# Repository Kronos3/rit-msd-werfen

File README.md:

# RIT-Werfen Inspection

## Overview

Layout for this project:
  - /pcb - KiCAD Design file for the PCB
  - /mc - Microcontroller firmware for STM32L476RG
  - /prototyping - Test images and Jupyter Notebooks used to prototype code
  - /src - Code running on the Raspberry Pi and in the browser
    - frontend/ - ReactJS (Typescript) program for frontend browser code
    - rit/ - Middleware that abstract the behavior of cameras and MC packet interface
    - web/ - FastAPI that exposes webendpoints for the frontend to submit requests to
    - camera_focusing.py - Script that boots up a QT Program to view the camera live

## Building

The microcontroller code can be built using CMake + GCC Arm toolchain.
You should use a relatively recent GCC Arm toolchain (`arm-none-eabi-gcc`)

### Dependency installation (Ubuntu)

On Ubuntu, run the following to install the dependencies:

```
sudo apt install gcc-arm-none-eabi cmake make
```

### Building PCB code

```
mkdir -p mc/build
cd mc/build
cmake -DCMAKE_C_COMPILER=arm-none-eabi-gcc -DCMAKE_CXX_COMPILER=arm-none-eabi-g++ ../
```

Now that the code is built, you can flash the PCB using an ST-Link or the ST-Link found on a STM32 Nucleo board using SWD via OpenOCD. I'd recommend using a Nucleo board for flashing along with an IDE like CLion that can set up, build and flash firmware for you.

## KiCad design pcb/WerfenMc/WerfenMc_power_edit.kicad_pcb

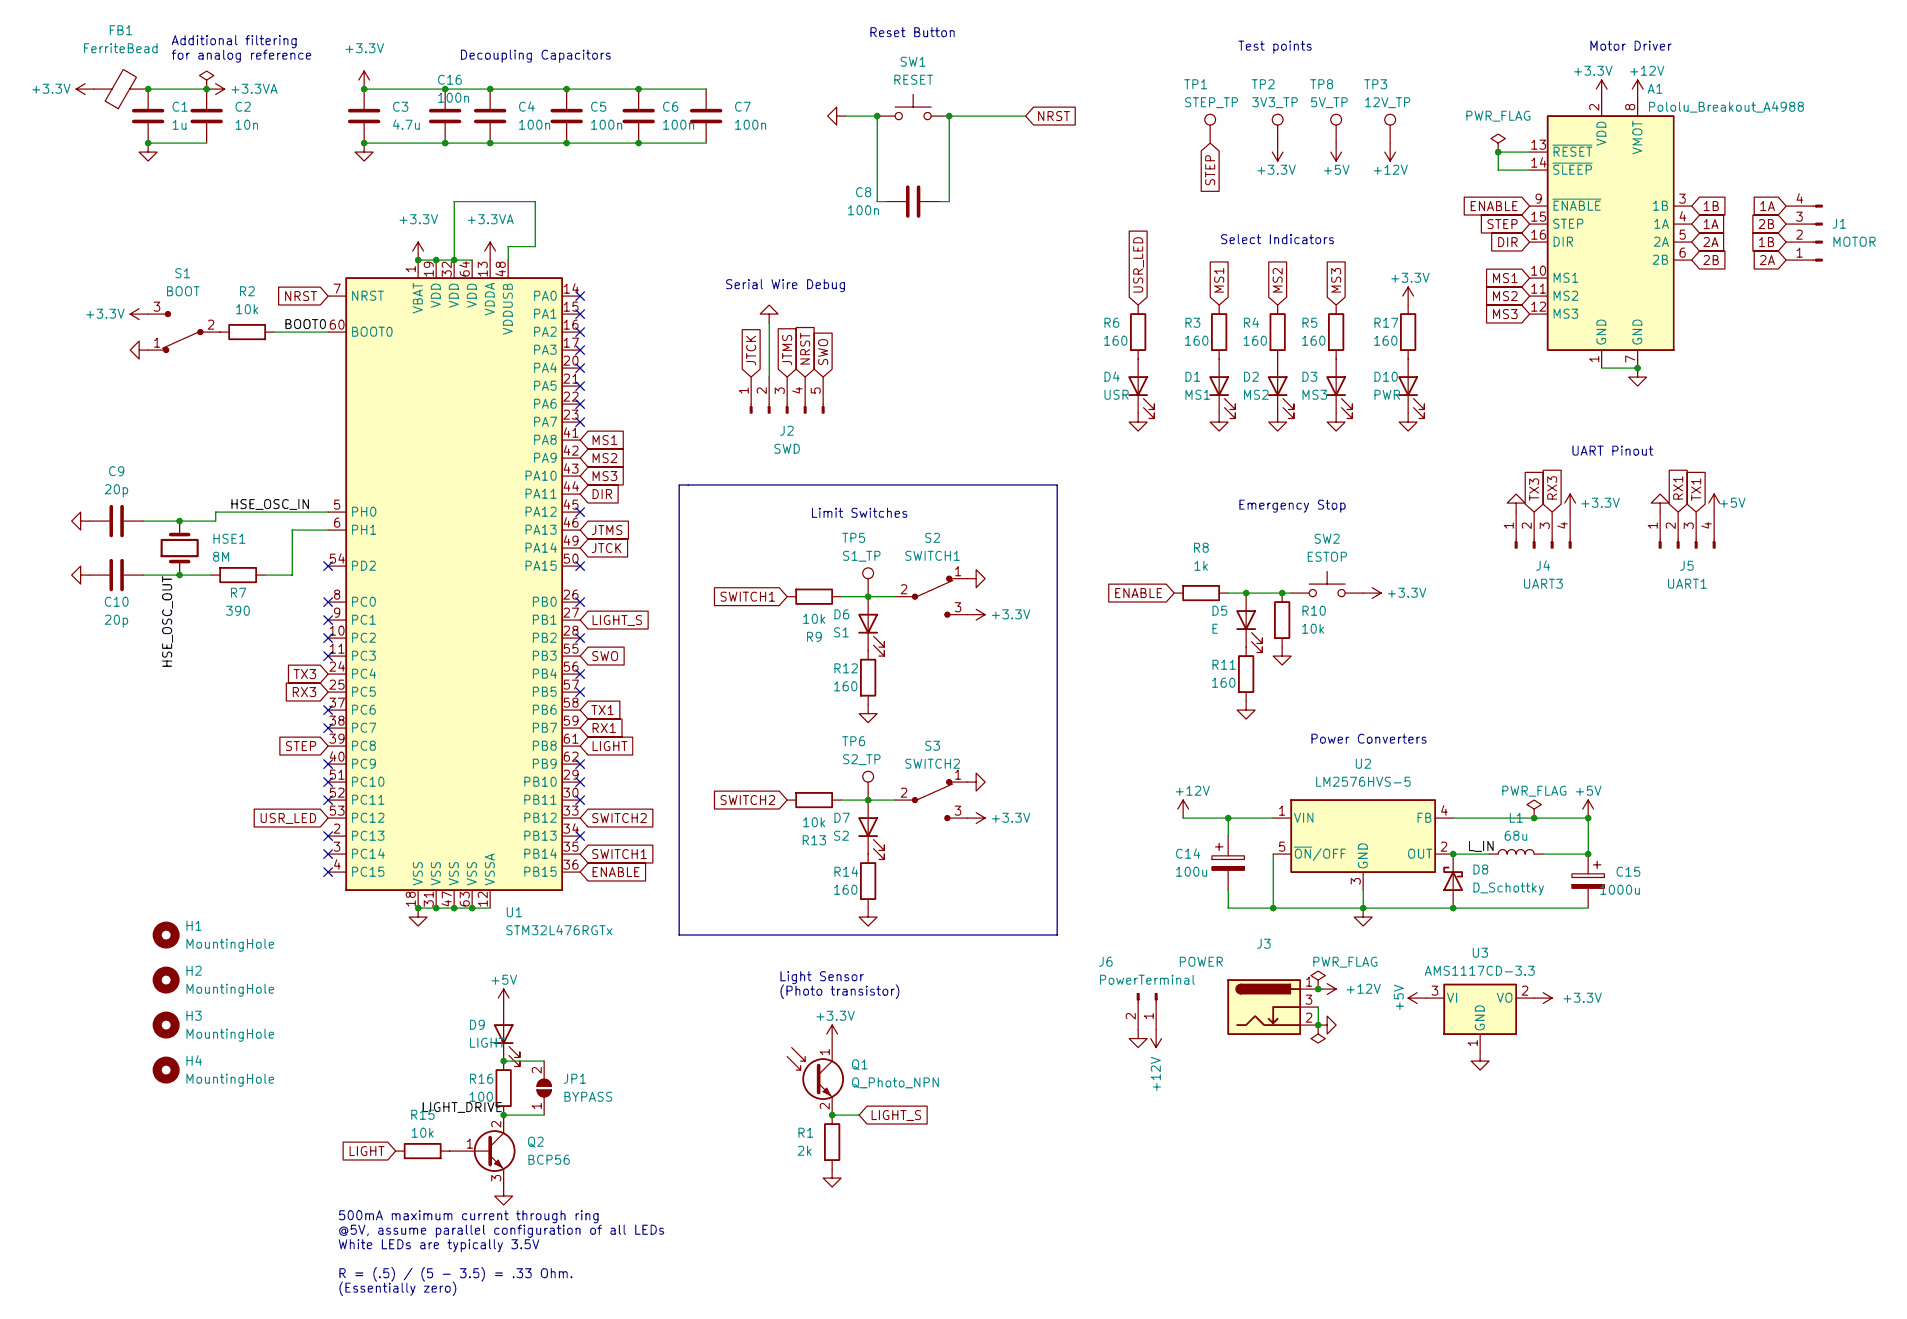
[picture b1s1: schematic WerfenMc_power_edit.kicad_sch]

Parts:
A1: Pololu_Breakout_A4988; Pololu_Breakout-16_15.2x20.3mm
C1: 1u; CP_EIA-2012-12_Kemet-R
C2: 10n; CP_EIA-2012-12_Kemet-R
C3: 4.7u; CP_EIA-2012-12_Kemet-R
C4, C5, C6, C7, C8, C16: 100n; C_0402_1005Metric
C9, C10: 20p; C_0402_1005Metric
C14: 100u; C_Elec_8x5.4
C15: 1000u; C_Elec_8x5.4
D1: MS1; LED_0805_2012Metric
D2: MS2; LED_0805_2012Metric
D3: MS3; LED_0805_2012Metric
D4: USR; LED_0805_2012Metric
D5: E; LED_0805_2012Metric
D6: S1; LED_0805_2012Metric
D7: S2; LED_0805_2012Metric
D8: D_Schottky; D_SMC
D9: LIGHT; TerminalBlock_Phoenix_MPT-0,5-2-2.54_1x02_P2.54mm_Horizontal
D10: PWR; LED_0805_2012Metric
FB1: FerriteBead; L_0603_1608Metric
H1, H2, H3, H4: MountingHole; MountingHole_2.2mm_M2
HSE1: 8M; Crystal_SMD_MicroCrystal_CC4V-T1A-2Pin_5.0x1.9mm
J1: MOTOR; PinHeader_1x04_P2.54mm_Vertical
J2: SWD; PinHeader_1x05_P2.54mm_Vertical
J3: POWER; BarrelJack_Horizontal
J4: UART3; PinHeader_1x04_P2.54mm_Vertical
J5: UART1; PinHeader_1x04_P2.54mm_Vertical
J6: PowerTerminal; TerminalBlock_Phoenix_MPT-0,5-2-2.54_1x02_P2.54mm_Horizontal
JP1: BYPASS; SolderJumper-2_P1.3mm_Open_Pad1.0x1.5mm
L1: 68u; SRP1040VA-1R5M
Q1: Q_Photo_NPN; PinHeader_1x02_P2.54mm_Vertical
Q2: BCP56; SOT-223
R1: 2k; R_Axial_DIN0411_L9.9mm_D3.6mm_P15.24mm_Horizontal
R2, R9, R10, R13, R15: 10k; R_0402_1005Metric
R3, R4, R5, R6, R11, R12, R14, R17: 160; R_0402_1005Metric
R7: 390; R_0402_1005Metric
R8: 1k; R_0402_1005Metric
R16: 100; R_0603_1608Metric
S1: BOOT; Switch_Slide_11.6x4mm_EG1218; MPN EG1218; Digi-Key_PN EG1903-ND
S2: SWITCH1; PinHeader_1x03_P2.54mm_Vertical; MPN EG1218; Digi-Key_PN EG1903-ND
S3: SWITCH2; PinHeader_1x03_P2.54mm_Vertical; MPN EG1218; Digi-Key_PN EG1903-ND
SW1: RESET; SW_PUSH_6mm
SW2: ESTOP; PinHeader_1x02_P2.54mm_Vertical
TP1: STEP_TP; TestPoint_Pad_D1.5mm
TP2: 3V3_TP; TestPoint_Pad_D1.5mm
TP3: 12V_TP; TestPoint_Pad_D1.5mm
TP5: S1_TP; TestPoint_Pad_D1.5mm
TP6: S2_TP; TestPoint_Pad_D1.5mm
TP8: 5V_TP; TestPoint_Pad_D1.5mm
U1: STM32L476RGTx; LQFP-64_10x10mm_P0.5mm
U2: LM2576HVS-5; TO-263-5_TabPin3
U3: AMS1117CD-3.3; TO-252-3_TabPin2

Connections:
1A: A1.4 (1A), J1.4
1B: A1.3 (1B), J1.2
2A: A1.5 (2A), J1.1
2B: A1.6 (2B), J1.3
+3.3V: A1.2 (VDD), C3.1, C4.1, C5.1, C6.1, C7.1, C16.1, FB1.1, J4.4, Q1.1 (C), R17.1, S1.3, S2.3, S3.3, SW2.2, TP2.1, U1.1 (VBAT), U1.19 (VDD), U1.32 (VDD), U1.48 (VDDUSB), U1.64 (VDD), U3.2 (VO)
+3.3VA: C1.1, C2.1, FB1.2, U1.13 (VDDA)
+5V: C15.1, D9.1 (A), J5.4, L1.2, TP8.1, U2.4 (FB), U3.3 (VI)
+12V: A1.8 (VMOT), C14.1, J3.1, J6.1, TP3.1, U2.1 (VIN)
/BOOT0: R2.2, U1.60 (BOOT0)
/HSE_OSC_IN: C9.2, HSE1.2, U1.5 (PH0)
/HSE_OSC_OUT: C10.2, HSE1.1, R7.2
/LIGHT_DRIVE: JP1.1 (A), Q2.2 (C), Q2.4 (C), R16.2
/L_IN: D8.1 (K), L1.1, U2.2 (OUT)
DIR: A1.16 (DIR), U1.44 (PA11)
ENABLE: A1.9 (~ENABLE), R8.2, U1.36 (PB15)
GND: A1.1 (GND), A1.7 (GND), C1.2, C2.2, C3.2, C4.2, C5.2, C6.2, C7.2, C8.2, C9.1, C10.1, C14.2, C15.2, C16.2, D1.1 (K), D2.1 (K), D3.1 (K), D4.1 (K), D8.2 (A), D10.1 (K), J2.2, J3.2, J3.3, J4.1, J5.1, J6.2, Q2.3 (E), R1.2, R10.2, R11.2, R12.2, R14.2, S1.1, S2.1, S3.1, SW1.1, U1.12 (VSSA), U1.18 (VSS), U1.31 (VSS), U1.47 (VSS), U1.63 (VSS), U2.3 (GND), U2.5 (~ON/OFF), U3.1 (GND)
JTCK: J2.1, U1.49 (PA14)
JTMS: J2.3, U1.46 (PA13)
LIGHT: R15.1, U1.61 (PB8)
LIGHT_S: Q1.2 (E), R1.1, U1.27 (PB1)
MS1: A1.10 (MS1), R3.1, U1.41 (PA8)
MS2: A1.11 (MS2), R4.1, U1.42 (PA9)
MS3: A1.12 (MS3), R5.1, U1.43 (PA10)
NRST: C8.1, J2.4, SW1.2, U1.7 (NRST)
unnamed: A1.13 (~RESET), A1.14 (~SLEEP)
unnamed: D1.2 (A), R3.2
unnamed: D2.2 (A), R4.2
unnamed: D3.2 (A), R5.2
unnamed: D4.2 (A), R6.2
unnamed: D5.1 (K), R11.1
unnamed: D5.2 (A), R8.1, R10.1, SW2.1
unnamed: D6.1 (K), R12.1
unnamed: D6.2 (A), R9.1, S2.2, TP5.1
unnamed: D7.1 (K), R14.1
unnamed: D7.2 (A), R13.1, S3.2, TP6.1
unnamed: D9.2 (K), JP1.2 (B), R16.1
unnamed: D10.2 (A), R17.2
unnamed: Q2.1 (B), R15.2
unnamed: R2.1, S1.2
unnamed: R7.1, U1.6 (PH1)
RX1: J5.2, U1.59 (PB7)
RX3: J4.3, U1.25 (PC5)
STEP: A1.15 (STEP), TP1.1, U1.39 (PC8)
SWITCH1: R9.2, U1.35 (PB14)
SWITCH2: R13.2, U1.33 (PB12)
SWO: J2.5, U1.55 (PB3)
TX1: J5.3, U1.58 (PB6)
TX3: J4.2, U1.24 (PC4)
USR_LED: R6.1, U1.53 (PC12)

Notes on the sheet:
UART Pinout
Serial Wire Debug
Additional filtering for analog reference
Test points
Decoupling Capacitors
Power Converters
500mA maximum current through ring @5V, assume parallel configuration of all LEDs White LEDs are typically 3.5V R = (.5) / (5 - 3.5) = .33 Ohm. (Essentially zero)
Select Indicators
Reset Button
Emergency Stop
Light Sensor (Photo transistor)
Motor Driver
Limit Switches

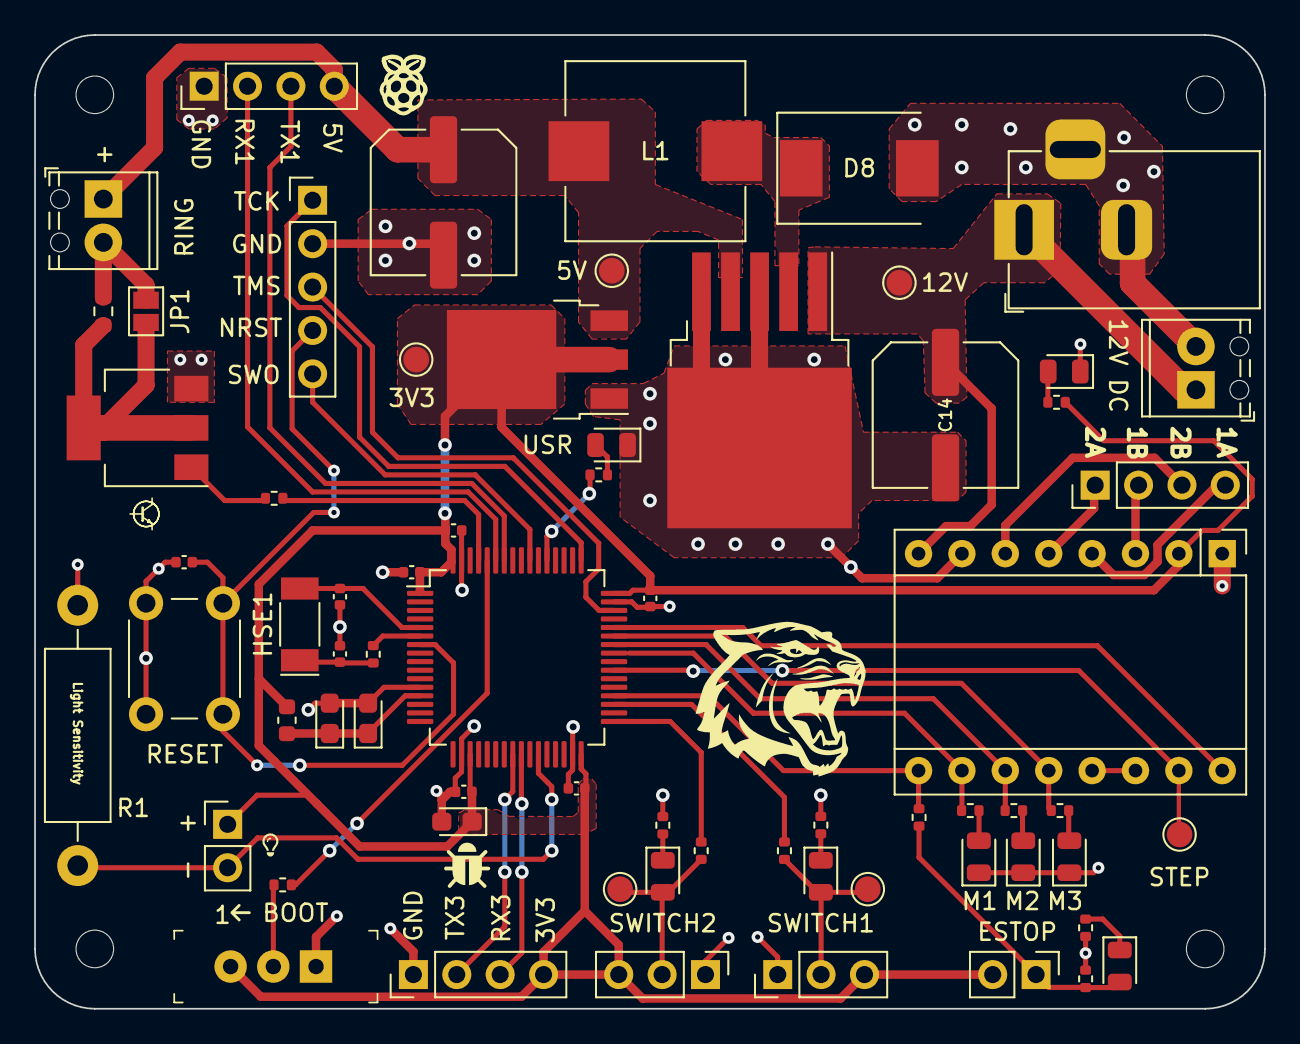
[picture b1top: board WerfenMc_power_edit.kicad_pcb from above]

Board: 2 copper layers, 72.0 x 57.0 mm, 71 parts (0 on the bottom side), 49 nets.

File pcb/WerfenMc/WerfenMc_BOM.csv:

Designator,Qnty,Comment,Name,Footprint,Description,JLCPCB Part #
"C1, ",1,1uF,C,Capacitor_Tantalum_SMD:CP_EIA-2012-12_Kemet-R,Unpolarized capacitor,C28323
"C2, ",1,10nF,C,Capacitor_Tantalum_SMD:CP_EIA-2012-12_Kemet-R,Unpolarized capacitor,C1710
"C3, ",1,4.7uF,C,Capacitor_Tantalum_SMD:CP_EIA-2012-12_Kemet-R,Unpolarized capacitor,C17779
"C4, C5, C6, C7, C8, C16, ",6,100nF,C,Capacitor_SMD:C_0402_1005Metric,Unpolarized capacitor,C1525
"C9, C10, ",2,20pF,C,Capacitor_SMD:C_0402_1005Metric,Unpolarized capacitor,C1554
"C14, ",1,100uF,C_Polarized,Capacitor_SMD:C_Elec_8x5.4,Polarized capacitor,C72481
"C15, ",1,1000uF,C_Polarized,Capacitor_SMD:C_Elec_8x5.4,Polarized capacitor,C99833
"D1, D2, D3, D4, D5, D6, D7, D10",8,LED Red,LED,LED_SMD:LED_0805_2012Metric,Light emitting diode,C84256
"D8,",1,D_Schottky,D_Schottky,Diode_SMD:D_0805_2012Metric,Schottky diode,C35722
"FB1, ",1,FerriteBead,FerriteBead,Inductor_SMD:L_0603_1608Metric,Ferrite bead,C1002
"HSE1, ",1,8MHz,Crystal,Crystal:Crystal_SMD_TXC_7A-2Pin_5x3.2mm,Two pin crystal,C115962
"Q2, ",1,BCP56,BCP56,Package_TO_SOT_SMD:SOT-223,"1A Ic, 80V Vce, NPN Medium Power Transistor, SOT-223",C95810
"R2, R9, R10, R13, R15, ",5,10k,R,Resistor_SMD:R_0402_1005Metric,Resistor,C25744
"R3, R4, R5, R6, R11, R12, R14, R17, ",8,160,R,Resistor_SMD:R_0402_1005Metric,Resistor,C25087
"R7, ",1,390,R,Resistor_SMD:R_0402_1005Metric,Resistor,C25102
"R8, ",1,1k,R,Resistor_SMD:R_0402_1005Metric,Resistor,C11702
"R16, ",1,100,R,Resistor_SMD:R_0603_1608Metric,Resistor,C22775
"U1, ",1,STM32L476RGTx,STM32L476RGTx,Package_QFP:LQFP-64_10x10mm_P0.5mm,"ARM Cortex-M4 MCU, 1024KB flash, 128KB RAM, 80MHz, 1.71-3.6V, 51 GPIO, LQFP-64",C74797
"U2, ",1,LM2576HVS-5,LM2576HVS-5,Package_TO_SOT_SMD:TO-263-5_TabPin3,"5V 3A, SIMPLE SWITCHER® Step-Down Voltage Regulator, High Voltage Input, TO-263",C234209
"U3, ",1,AMS1117CD-3.3,AMS1117CD-3.3,Package_TO_SOT_SMD:TO-252-3_TabPin2,"1A Low Dropout regulator, positive, 3.3V fixed output, TO-252",C841796

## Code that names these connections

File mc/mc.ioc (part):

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Mcu.Name=STM32L476R(C-E-G)Tx
Mcu.Package=LQFP64
Mcu.UserName=STM32L476RGTx
PA10.GPIOParameters=GPIO_Label
PA10.GPIO_Label=MS3
PA10.Signal=GPIO_Output
PA11.GPIOParameters=GPIO_Label
PA11.GPIO_Label=DIR
PA11.Signal=GPIO_Output
PA13\ (JTMS-SWDIO).GPIOParameters=GPIO_Label
PA13\ (JTMS-SWDIO).GPIO_Label=TMS
PA13\ (JTMS-SWDIO).Mode=Serial_Wire
PA13\ (JTMS-SWDIO).Signal=SYS_JTMS-SWDIO
PA14\ (JTCK-SWCLK).GPIOParameters=GPIO_Label
PA14\ (JTCK-SWCLK).GPIO_Label=TCK
PA14\ (JTCK-SWCLK).Mode=Serial_Wire
PA14\ (JTCK-SWCLK).Signal=SYS_JTCK-SWCLK
PA8.GPIOParameters=GPIO_Label
PA8.GPIO_Label=MS1
PA8.Signal=GPIO_Output
PA9.GPIOParameters=GPIO_Label
PA9.GPIO_Label=MS2
PA9.Signal=GPIO_Output
PB1.GPIOParameters=GPIO_Label
PB1.GPIO_Label=LIGHT_S
PB1.Signal=ADCx_IN16
PB12.GPIOParameters=GPIO_Label,GPIO_ModeDefaultEXTI
PB12.GPIO_Label=SWITCH2
PB12.GPIO_ModeDefaultEXTI=GPIO_MODE_IT_RISING
PB12.Signal=GPXTI12
PB14.GPIOParameters=GPIO_Label
PB14.GPIO_Label=SWITCH1
PB14.Signal=GPXTI14
PB15.GPIOParameters=GPIO_Label,GPIO_ModeDefaultEXTI
PB15.GPIO_Label=ENABLE
PB15.GPIO_ModeDefaultEXTI=GPIO_MODE_IT_RISING
PB15.Signal=GPXTI15
PB3\ (JTDO-TRACESWO).GPIOParameters=GPIO_Label
PB3\ (JTDO-TRACESWO).GPIO_Label=SWO
PB3\ (JTDO-TRACESWO).Signal=SYS_JTDO-SWO
PB6.Mode=Asynchronous
PB6.Signal=USART1_TX
PB7.Mode=Asynchronous
PB7.Signal=USART1_RX
PB8.GPIOParameters=GPIO_Label
PB8.GPIO_Label=LIGHT
PB8.Signal=S_TIM4_CH3
PC12.GPIOParameters=GPIO_Label
PC12.GPIO_Label=LED
PC12.Signal=GPIO_Output
PC4.Mode=Asynchronous
PC4.Signal=USART3_TX
PC5.Mode=Asynchronous
PC5.Signal=USART3_RX
PC8.GPIOParameters=GPIO_Label
PC8.GPIO_Label=STEP
PC8.Signal=S_TIM3_CH3
PH0-OSC_IN\ (PH0).Signal=RCC_OSC_IN
PH1-OSC_OUT\ (PH1).Signal=RCC_OSC_OUT
RCC.HSE_VALUE=8000000
RCC.SYSCLKFreq_VALUE=80000000
RCC.SYSCLKSource=RCC_SYSCLKSOURCE_PLLCLK
board=NUCLEO-L476RG
boardIOC=true

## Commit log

2022-09-14 Add prototyping scripts
2022-09-14 Added training set generator
2022-09-14 Added python requirements
2022-09-15 Working text recognition
2022-09-20 Added initial code
2022-09-21 Working minimal build
2022-09-21 Added fprime vscode extension
2022-09-25 Mark vendored headerse
2022-09-25 Clean up readme and CMakeLists
2022-09-25 Added more sequenceres, connected camera to videoStreamer
2022-09-25 Added makefile for seq compilation, fixed seqs for new dict
2022-09-25 Added fsw sync, updated readme
2022-10-06 Added real werfen images
2022-10-28 Initial Camera implementation
2022-11-04 Still and Video camera streams
2022-11-14 Started python switch
2022-11-17 Initial qt ui
2023-01-19 Started motor driver
2023-01-19 Update ui
2023-01-19 Finished motor_step commanding
2023-01-23 Support absolute and relative
2023-01-24 Timer based motor driver
2023-02-01 Updte
2023-02-01 Running motor
2023-02-06 Count motor steps
2023-02-06 updated-working-motor
2023-02-06 Not working
2023-02-08 Switched to stm32l476rg chip
2023-02-15 Design PCB, switch to L4 chip
2023-02-15 Exported step file
2023-02-15 Added a via to motor driver ground, exported better step file
2023-03-02 Finished packet_task, wrote led voltage controller, write pi side driver
2023-03-02 Code cleanup
2023-03-02 Expose home, added help
2023-03-02 Turn off ms line LEDs after motor request is done
2023-03-02 Implemented absolute commanding, turn off LEDs when motor is finished
2023-03-02 Allow sending step size via cli
2023-03-03 Added docstring to all functions in stage
2023-03-06 Working stage
2023-03-06 250 Hz step
2023-03-08 Reverse engineer the actual layout with the new schottkey (whoops)
2023-03-08 Implement dynamic motor trigger
2023-03-09 Implement debounce on limit switches, long commands, stage wait for finish, motor stop
2023-03-09 Implemented sequence
2023-03-09 Wrote cam driver
2023-03-09 Granular waits between sensor moves
2023-03-09 Added aux cam tesseract code
2023-03-20 Python 3.9 updates
2023-03-22 Working image capture on pi
2023-04-03 Flush serial buffers before sending packet
2023-04-05 Started gui and fastapi
2023-04-05 Init main.py with correct hardware
2023-04-05 Add python requirements
2023-04-05 Web response update
2023-04-05 Use a streaming response for images
2023-04-05 Try to make this run faster
2023-04-05 This is the way
2023-04-05 Fix path
2023-04-05 Add start stop routes
2023-04-05 Fix dummy serial driver
2023-04-05 Fix image encoding
2023-04-05 Include option to buffer all images
2023-04-05 Don't encode image during buffering
2023-04-05 Allow zero delay
2023-04-05 Updates gui
2023-04-05 Swap ui for reactjs
2023-04-05 Add more functions to react
2023-04-05 Set dummy via cli
2023-04-05 Fix warning
2023-04-05 Fix checksum issue in firmware
2023-04-05 Added status, added software estop
2023-04-06 Tell streaming response about image sizes
2023-04-06 Use big endian for file size
2023-04-06 Allow serial override
2023-04-06 Downscale 20% all images
2023-04-06 Add limit switch step off
2023-04-06 Implemented limit_step_off in middleware
2023-04-06 Implement multi images xfer using future manager
2023-04-06 Working single card
2023-04-06 Run single_card in the asyncio event loop so that it can create fids
2023-04-06 Add react key for imgs, use jpeg by default
2023-04-06 Serve built frontend from fastapi
2023-04-06 Fix static serve
2023-04-06 Unignore prog files
2023-04-06 Default middleware address is window location
2023-04-06 Rebuild frontend
2023-04-06 Fix colormappings
2023-04-06 Allow negative absolute positions
2023-04-10 Build using vite
2023-04-10 Dont use a stylesheet
2023-04-10 Add failure flag to indicate limit switch hit
2023-04-10 Use vite production build location for static serve
2023-04-10 Use correct launch script for debug
2023-04-10 No CSS is needed
2023-04-10 Working step off
2023-04-10 Add scaling param to single card
2023-04-10 Add scale before super call
2023-04-10 Turn off awb
2023-04-10 Do it right
2023-04-11 Wrote alignment code
2023-04-11 Add error text to form response
2023-04-12 Use post request for align
2023-04-12 Fix schema
2023-04-12 Fix response
2023-04-12 Fix messages
2023-04-12 More log fixes
2023-04-12 Default image encoding
2023-04-12 Dont scale image again
2023-04-12 Update alignment algo
2023-04-12 Better alignment error finding, added edge num points threshold
2023-04-12 Handle no laplace points
2023-04-12 Fix arguments
2023-04-12 Reject extreme edges
2023-04-12 Add more debug
2023-04-12 Handle non points
2023-04-12 Add delay between steps
2023-04-12 Actually fix npoints
2023-04-12 More debug
2023-04-12 Add another delay
2023-04-12 Simplfy
2023-04-12 Fix return
2023-04-12 Fix fine motion
2023-04-12 Added card ID to frontend
2023-04-12 Update card_id
2023-04-12 stuff
2023-04-12 More stuff
2023-04-12 No output
2023-04-12 deep deep deep
2023-04-12 Param
2023-04-12 Add scale factor to card_di
2023-04-12 Handle errors better
2023-04-13 Add USB listing to middle
2023-04-13 Correct the init
2023-04-13 Added calibrated flag to PCB
2023-04-13 Add calibrated to frontend
2023-04-13 Rebuilt frontend
2023-04-13 Fix fault on limit
2023-04-13 Add unmount button
2023-04-13 Ask for alignment if not calibrated
2023-04-14 UI overhaul
2023-04-14 Added main program running
2023-04-14 Better state update
2023-04-14 Fix better status ping
2023-04-14 Fix some async
2023-04-14 Allow default single card params
2023-04-14 Get around tess not installed
2023-04-14 Fix absolute approach
2023-04-14 Fixed file output
2023-04-15 Show image previews on acquire
2023-04-15 Allow rename
2023-04-15 Allow renaming in frontend
2023-04-15 Use str for card_id
2023-04-15 Fix rename
2023-04-15 Fix refresh deps
2023-04-15 Fixed rename frontend
2023-04-15 Perform encode during stage motion
2023-04-15 Fix form settings
2023-04-15 Fix image memory leak
2023-04-15 Encode in parallel
2023-04-15 Whoops approach absolute
2023-04-15 Speed things up
2023-04-16 Add eslint
2023-04-16 Fix get_cards
2023-04-16 Added image preview request
2023-04-16 Added delete card endpoint
2023-04-16 Working view
2023-04-16 Add file download endpoint
2023-04-16 Add download calal
2023-04-16 Update zip call
2023-04-16 Remove archive before creating it
2023-04-16 zip call
2023-04-16 Build for download file
2023-04-16 Project cleanup
2023-04-16 Clean up git vendoring
2023-04-16 Use memo for schema generation
2023-04-17 Fix unload query
2023-04-17 Initial pose approach use correct step size
2023-04-17 Card_id dev cleanu
2023-04-17 Update card_id defaults
2023-04-17 Another fix
2023-04-17 Change light level before motion for id
2023-04-17 Don't keep aux cam running
2023-04-17 Individually set each position
2023-04-17 Use relative
2023-04-17 Set as qp
2023-04-17 Globally swap colormaps
2023-04-17 Less contrained threshing
2023-04-17 Update frontend
2023-04-17 Fix defaults
2023-04-17 Jenk it up
2023-04-17 Dejenking
2023-04-17 Better defaults
2023-04-17 Card id defaults
2023-04-17 Update more defaults
2023-04-18 Allow alignment code debugging
2023-04-18 Fix async
2023-04-18 Use queue in async
2023-04-18 Dont use asyncio for queues
2023-04-18 Show processed img
2023-04-18 Crop garbage
2023-04-18 Pure laplacian
2023-04-18 Fix everything
2023-04-18 View orig
2023-04-18 Use scale
2023-04-18 Fix no_debug_align
2023-04-18 Fix it felix
2023-04-18 Fine step
2023-04-18 Everything working now
2023-04-18 Added start script
2023-04-19 New build
2023-04-19 Use int
2023-04-19 Add qt preview
2023-04-19 Force DRM
2023-04-21 Cleaner error handling
2023-04-21 Update for older opencv
2023-04-21 Correct preview
2023-04-21 Added focus buttons
2023-04-22 Added stage controls on focus
2023-04-22 Visual feedback on status ping
2023-04-24 Use correct method
2023-04-24 Correct low-res dims
2023-04-24 Another res set
2023-04-24 Correct ar for imx477
2023-04-24 Invert directions
2023-04-24 Added cam status thingy
2023-04-24 Fix error handling
2023-04-24 More robust
2023-04-24 Fix deps in lr
2023-04-24 Add icon
2023-04-24 Add notification for pcb failures
2023-04-26 Add scaling option to image acquire
2023-04-26 Fix card_id
2023-04-26 Light level
2023-05-01 Vendored
2023-05-01 More vendoring
2023-05-01 Even more vendoring

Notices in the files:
parts and their libraries:
Copyright 2021 Accelerated Designs. All rights reserved.
